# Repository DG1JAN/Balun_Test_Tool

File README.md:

# Balun_Test_Tool
Schematic and PCB of an easy test tool for Balun's and Unun's

Update to V1.1 - Changed the Design to THT Resistors after feedback from OMs

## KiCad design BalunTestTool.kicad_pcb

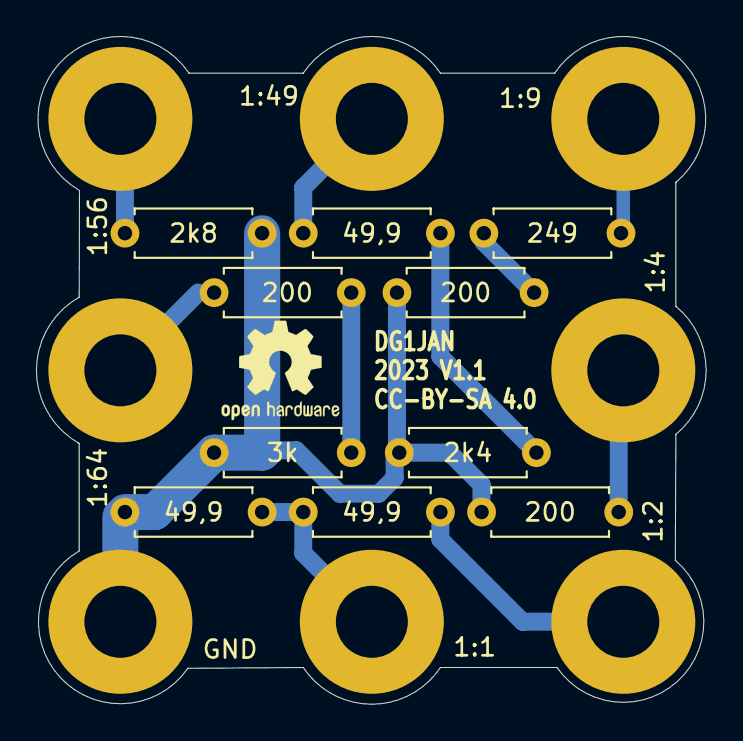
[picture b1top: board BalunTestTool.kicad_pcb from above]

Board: 2 copper layers, 37.2 x 37.1 mm, 18 parts (0 on the bottom side), 11 nets.

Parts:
1:1: 1:1; MountingHole_4mm_Pad
1:2: 1:2; MountingHole_4mm_Pad
1:4: 1:4; MountingHole_4mm_Pad
1:9: 1:9; MountingHole_4mm_Pad
1:49: 1:49; MountingHole_4mm_Pad
1:56: 1:56; MountingHole_4mm_Pad
1:64: 1:64; MountingHole_4mm_Pad
GND: GND; MountingHole_4mm_Pad
R1, R2, R7: 49,9; R_Axial_DIN0207_L6.3mm_D2.5mm_P7.62mm_Horizontal
R3, R4, R10: 200; R_Axial_DIN0207_L6.3mm_D2.5mm_P7.62mm_Horizontal
R5: 249; R_Axial_DIN0207_L6.3mm_D2.5mm_P7.62mm_Horizontal
R6: 2k4; R_Axial_DIN0207_L6.3mm_D2.5mm_P7.62mm_Horizontal
R8: 2k8; R_Axial_DIN0207_L6.3mm_D2.5mm_P7.62mm_Horizontal
R9: 3k; R_Axial_DIN0207_L6.3mm_D2.5mm_P7.62mm_Horizontal

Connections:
unnamed: GND.1, R1.2, R3.2, R4.2, R6.2, R8.2, R9.2
unnamed: 1:1.1, R1.1, R2.2
unnamed: 1:2.1, R2.1
unnamed: 1:4.1, R3.1
unnamed: 1:9.1, R5.1
unnamed: 1:49.1, R7.1
unnamed: 1:56.1, R8.1
unnamed: 1:64.1, R10.1
unnamed: R4.1, R5.2
unnamed: R6.1, R7.2
unnamed: R9.1, R10.2

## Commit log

2022-07-07 Add files via upload
    Initial Upload
2023-03-21 update new version with THT resistors
2023-03-21 update pictures
2023-04-14 deleted: BalunTestTool.kicad_pcb deleted: BalunTestTool.sch deleted: BalunTestTool_3d.png deleted: Gerber_BalunTestTool.zip deleted: Schematic.png deleted: old/BalunTestTool.kicad_pcb deleted: old/Ba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
2023-04-14 new file: BalunTestTool.kicad_pcb new file: BalunTestTool.kicad_prl new file: BalunTestTool.kicad_pro new file: BalunTestTool.kicad_sch new file: BalunTestTool_Gerber.zip new file: PCB_3dPicture.jpg 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

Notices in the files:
BalunTestTool.kicad_pcb:
CC-BY-SA 4.0
